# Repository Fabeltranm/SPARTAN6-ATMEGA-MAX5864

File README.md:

# SPARTAN6-ATMEGA-MAX5864

PINOUT

CONECTOR P1

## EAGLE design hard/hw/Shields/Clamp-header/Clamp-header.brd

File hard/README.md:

# READ TODO.md
## Last update 27/05

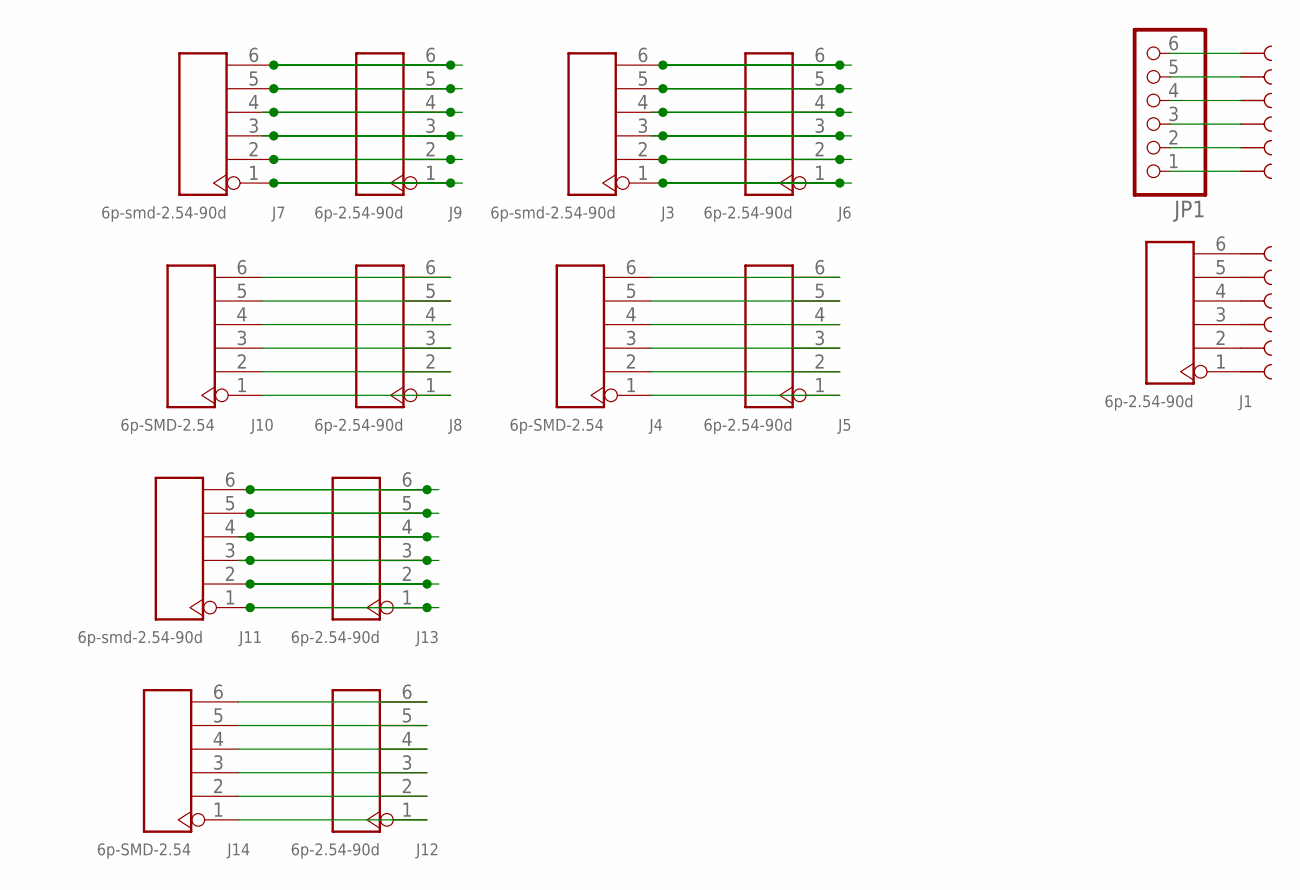
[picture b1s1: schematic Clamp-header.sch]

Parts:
J1, J5, J6, J8, J9, J12, J13: 6p-2.54-90d; H6-2.54-90D-FEMALE
J3, J7, J11: 6p-smd-2.54-90d; H6-SMD-MALE-2.54-90D
J4, J10, J14: 6p-SMD-2.54; H6-SMD-2.54
JP1: PINHD-1X6/90; 1X06/90
U$1, U$2, U$3, U$4, U$5, U$6, U$7, U$35, U$37, U$39, U$41, U$51: SEWTAP1; SEWTAP

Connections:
unnamed: J1.6, U$51.1
unnamed: J1.5, U$41.1
unnamed: J1.4, U$35.1
unnamed: J1.3, U$37.1
unnamed: J1.2, U$39.1
unnamed: J1.1, U$4.1
unnamed: JP1.6, U$3.1
unnamed: JP1.5, U$6.1
unnamed: JP1.4, U$7.1
unnamed: JP1.3, U$1.1
unnamed: JP1.2, U$5.1
unnamed: JP1.1, U$2.1
unnamed: J3.6, J6.6
unnamed: J3.5, J6.5
unnamed: J3.4, J6.4
unnamed: J3.3, J6.3
unnamed: J3.2, J6.2
unnamed: J3.1, J6.1
unnamed: J4.6, J5.6
unnamed: J4.5, J5.5
unnamed: J4.4, J5.4
unnamed: J4.3, J5.3
unnamed: J4.2, J5.2
unnamed: J4.1, J5.1
unnamed: J7.6, J9.6
unnamed: J7.5, J9.5
unnamed: J7.4, J9.4
unnamed: J7.3, J9.3
unnamed: J7.2, J9.2
unnamed: J7.1, J9.1
unnamed: J8.6, J10.6
unnamed: J8.5, J10.5
unnamed: J8.4, J10.4
unnamed: J8.3, J10.3
unnamed: J8.2, J10.2
unnamed: J8.1, J10.1
unnamed: J11.6, J13.6
unnamed: J11.5, J13.5
unnamed: J11.4, J13.4
unnamed: J11.3, J13.3
unnamed: J11.2, J13.2
unnamed: J11.1, J13.1
unnamed: J12.6, J14.6
unnamed: J12.5, J14.5
unnamed: J12.4, J14.4
unnamed: J12.3, J14.3
unnamed: J12.2, J14.2
unnamed: J12.1, J14.1

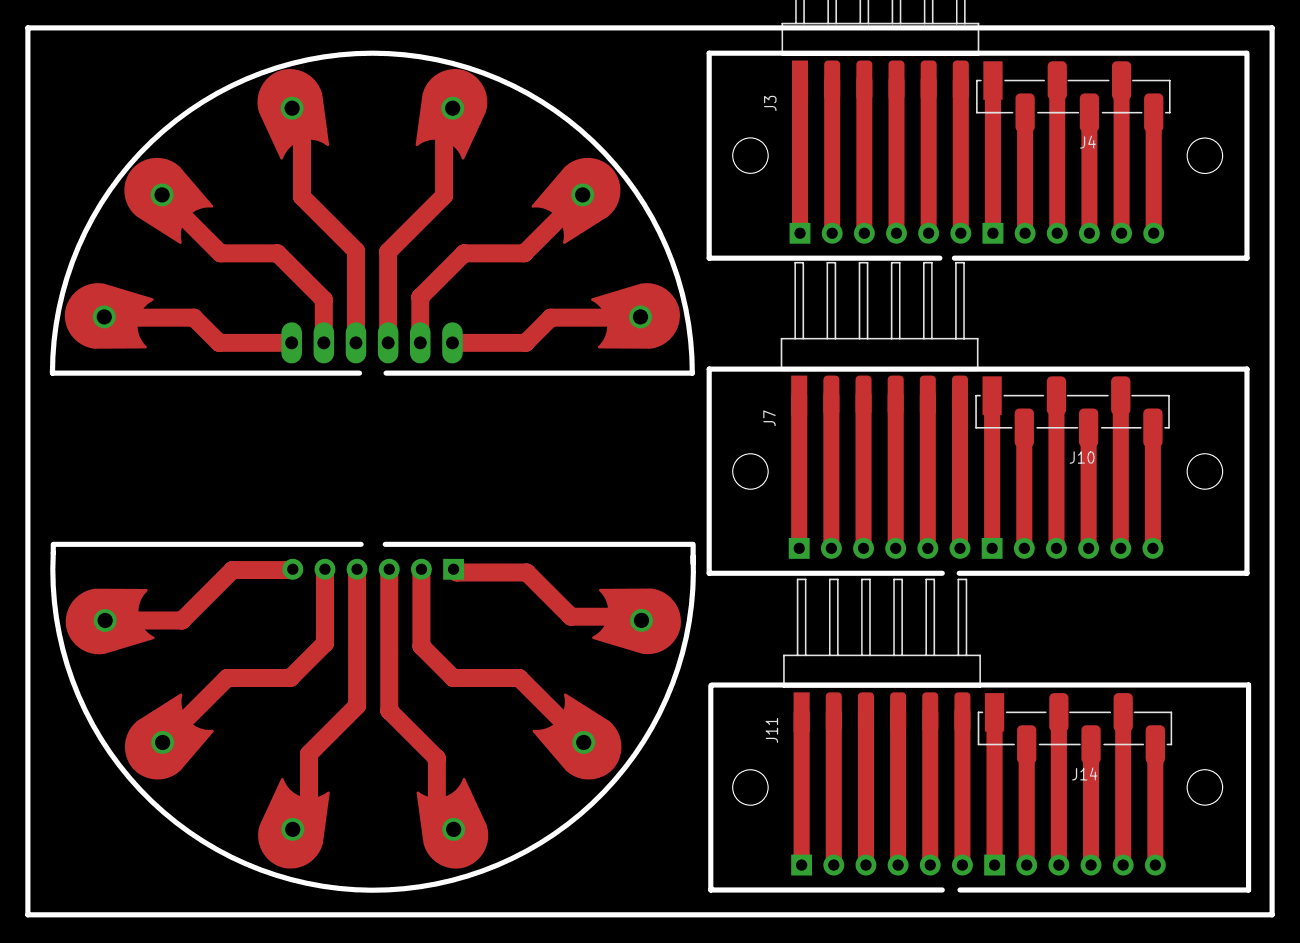
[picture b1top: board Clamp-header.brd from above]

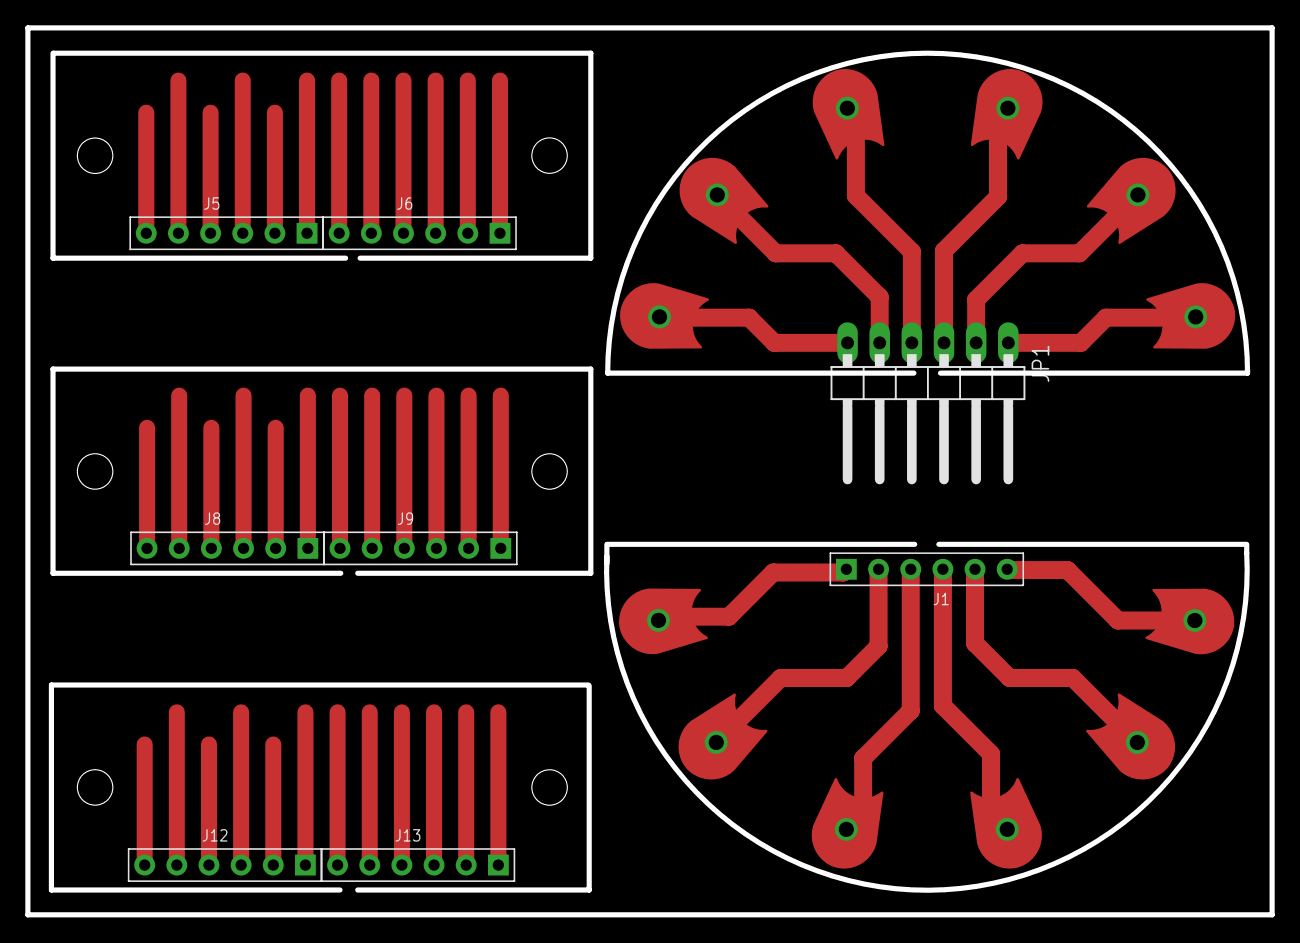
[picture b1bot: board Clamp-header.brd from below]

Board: 2 copper layers, 98.3 x 70.1 mm, 26 parts (8 on the bottom side), 48 nets.

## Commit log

2017-01-23 init
2017-01-31 Create bas
2017-02-02 version0.0
2017-02-02 deleted
    Please enter the commit message for your changes. Lines starting
2017-02-06 nuevo nombre
2017-02-06 Agregando nuevas hojas jerarquicas
    Hojas agregadas: Power y Audio
2017-02-06 Bloque de Audio
    Bloque de Audio implementado PAM8302 de adafruit:
    https://www.adafruit.com/product/2130
2017-02-06 Actualizacion Power
2017-02-06 Power: fuente de 5v - 2A
    by Luis Yaya
2017-02-07 ok 3d
2017-02-07 Actualizaciòn vista 3D
2017-02-08 Fuente 12V
    by Luis Yaya
2017-02-08 Actualización PinOut LVDS
    by Rubén Parra
2017-02-09 Datasheets
    By Rubén
2017-02-09 Actualizacion Raiz
    por Rubén
2017-02-10 Actualización Raiz
    by Rubén
2017-02-14 Actualizacion ref. DigitKey
    by Rubén
2017-02-14 Actualización SDRAM
2017-02-14 Actualización huellas y fusible
    by Rubén
2017-02-15 todas las huellas
    by Ruben
2017-02-16 Organizando PIN OUT vr.:0.1
    by Ruben
2017-02-17 Shields: Clamp-header
    Modificacion diametro de orificio pasante para tornillo 1/8
2017-02-20 Terminado Shield
    by Ruben
2017-02-20 Actualizacion Datasheet
2017-02-22 shield corregido
2017-02-22 shield 2.0
2017-02-27 Alimentacion Pantalla
2017-02-27 Clamp gerber update
2017-02-27 Todos los componentes en la tarjeta
    by Ruben
2017-02-28 Correccion Shield Clamp
    by Ruben
2017-03-03 LVDS ultimate test
    by LUIS
2017-03-04 Update board
    by Ruben
2017-03-09 Actualización K3
    by Ruben
2017-03-14 ProgRpiI2C
2017-03-14 Datasheets
2017-03-14 Revert "Datasheets"
    This reverts commit edbb8b8abfee325c3b920922dc11246233119ce4.
2017-03-14 Datasheet
2017-03-15 Revert "Revert "Datasheets""
    This reverts commit cc850c74b615b4119cf9ee2c458186102debd915.
2017-03-16 Revert "Revert "Revert "Datasheets"""
    This reverts commit 8b7c1ae5629daf9b9925dc53a42c9cad6393ae71.
2017-03-23 v1.0
2017-03-23 .gitignore
2017-05-18 Add ADC
2017-05-19 librarys
2017-05-30 Update supply power
2017-05-30 update 29 MAY
2017-05-30 Corrección esquematico
2017-05-30 Correccion SCH
2017-05-30 update TODO
2017-05-31 2x40 .
2017-05-31 2xx40 conn
2017-05-31 Add 3d model
2017-05-31 update 3d models
2017-06-01 reorganización
2017-06-05 update layout
2017-06-05 Test LVDS RAM
2017-06-05 Add jmp Rpi Power
2017-06-06 config power
2017-07-08 se modifican el pin hdmi- las resitencias RN1 - eñ conector de voltaje
2017-07-10 cambios en el pinout para HDMI-LVDS tarjeta HDMI Spartan6
2017-07-10 archivo de prueba
2017-07-13 cambios para que fuencione la pantalla de 18 bits
2017-07-13 ajustes para configuracion de la pantalla 13.3"
2017-07-17 cambios en el pinout de la FPGA para uso del puerto HDMI
2017-08-01 ok lvds and hdmi
2017-09-21 Changes in HDMISpartan6_Board
2017-09-28 versión 1.0
2017-09-28 v1-0
2017-09-29 version1.oo1
2017-09-30 add gerber files
2017-10-06 versión final
2017-10-06 all connected
2017-10-13 silkS progresing
2017-10-23 SilkS 2
2017-10-23 SilkS 2.1
2017-10-24 cambio de la memoria flash, referecnia y encapsulado
2017-10-25 conexión de la memoria flash y verificación del plano de tierras
2018-07-03 nueva Tarjeta
2018-08-04 change all board files
2018-11-15 se cambia la referencia del resonador XF2, queda pendiente actualizar la huella
2018-11-15 add file
2018-11-16 modificardo cF7 y cF8 a 33 pf
2018-12-04 error array resistencia hdm footprint 1206 error ...se debe cambiar
2019-02-05 add Docs
2019-02-06 docs img pinout
2019-02-28 add pinout P! imagen
2019-02-28 add readme
2019-02-28 add readme1
2019-03-04 add esquema
2019-08-12 add ejemplos
2019-08-12 add labs
2019-08-12 add primi
2019-08-19 sum4b
2019-08-19 add s
2019-08-20 test
2019-08-20 test2
2019-08-21 mapeo
2019-08-21 c mapeo
2019-08-21 add map
2019-08-21 add presentaciones
2019-08-21 add basys2
2019-08-21 add sum4b
2019-08-21 add nu
2019-08-21 add ise
2019-08-26 add ejemplo03
2019-08-28 ok lb3
2019-09-10 ADD A,B,C
2019-09-15 add
    add ej 4 3
2019-09-15 aa
    a
2019-10-17 add
    add ej7
2019-10-18 lb08
    0
2019-10-18 lab08
2019-10-23 lb9
    l9
